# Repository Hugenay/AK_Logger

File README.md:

AK_Logger
=========

test

eine weitere Änderung um zu testen was passiert wenn beide ändern

bla

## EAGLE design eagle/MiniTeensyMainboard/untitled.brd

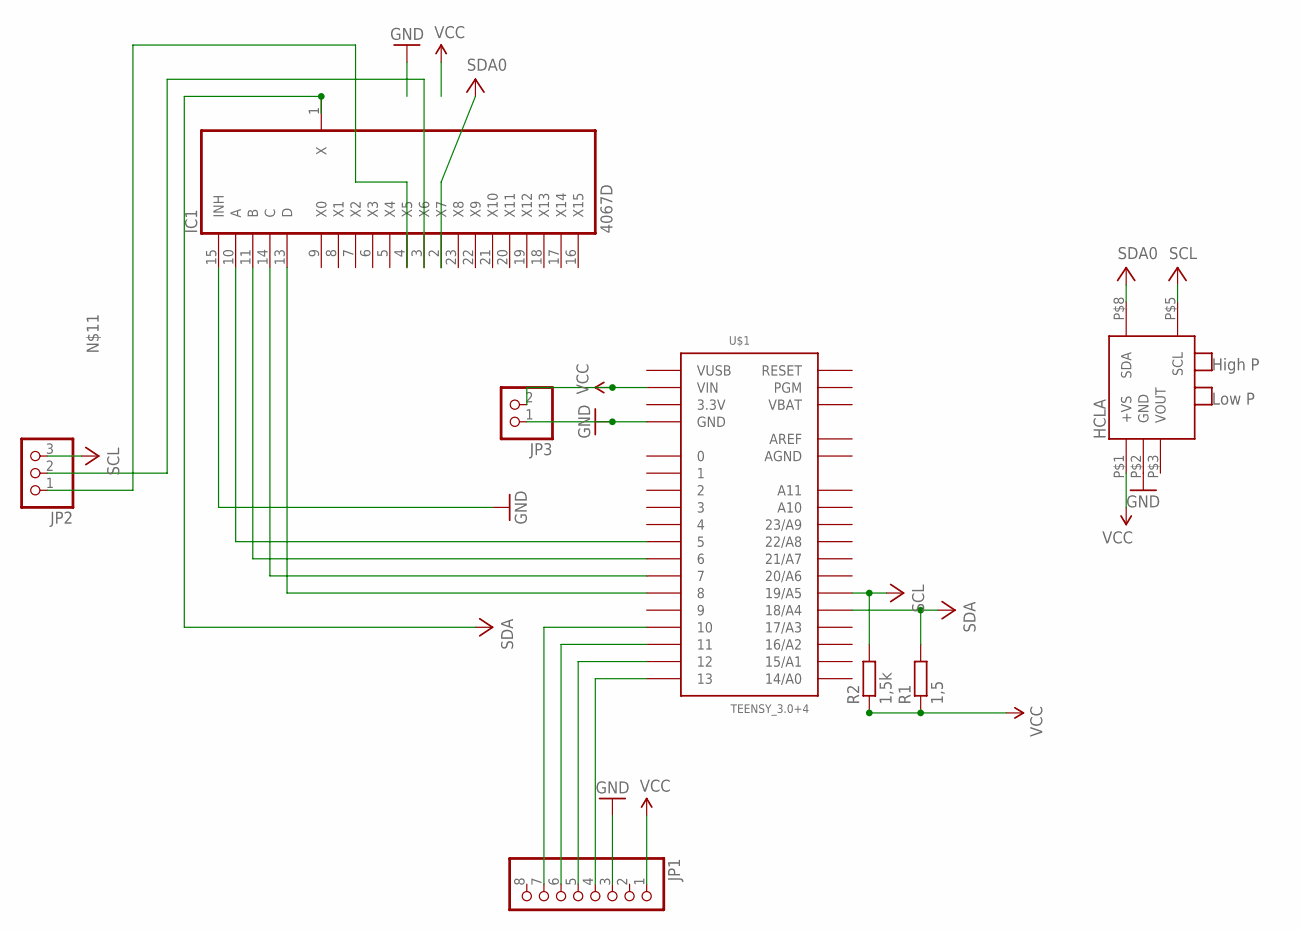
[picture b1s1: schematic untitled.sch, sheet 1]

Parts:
IC1: 4067D; SO24W
JP1: PINHD-1X8; 1X08
JP2: PINHD-1X3; 1X03
JP3: PINHD-1X2; 1X02
R1: 1,5; 0204/5
R2: 1,5k; 0204/5
U$1: TEENSY_3.0+4
U$2: HCLA

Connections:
3.3V: U$1.3.3V, U$1.3.3V1 (3.3V)
AGND: U$1.AGND
AREF: U$1.AREF
GND: IC1.15 (INH), JP1.3, JP3.1, U$1.GND, U$1.GND1 (GND), U$2.P$2 (GND)
unnamed: IC1.10 (A), U$1.5
unnamed: IC1.11 (B), U$1.6
unnamed: IC1.14 (C), U$1.7
unnamed: IC1.13 (D), U$1.8
unnamed: JP1.7, U$1.10
unnamed: JP1.6, U$1.11
unnamed: JP1.5, U$1.12
unnamed: JP1.4, U$1.13
unnamed: IC1.4 (X5), JP2.1
unnamed: IC1.3 (X6), JP2.2
SCL: JP2.3, R2.2, U$1.19/A5, U$2.P$5 (SCL)
SDA: IC1.1 (X), R1.2, U$1.18/A4
SDA0: IC1.2 (X7), U$2.P$8 (SDA)
VBAT: U$1.VBAT
VDD: IC1.24 (VDD), JP1.1, JP3.2, R1.1, R2.1, U$1.VIN, U$2.P$1 (+VS)
VSS: IC1.12 (VSS)
VUSB: U$1.VUSB

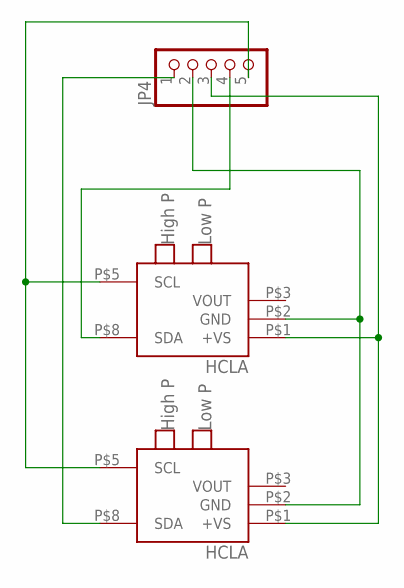
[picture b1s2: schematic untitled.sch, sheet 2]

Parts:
JP4: PINHD-1X5; 1X05
U$3, U$4: HCLA

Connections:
unnamed: JP4.5, U$3.P$5 (SCL), U$4.P$5 (SCL)
unnamed: JP4.3, U$3.P$1 (+VS), U$4.P$1 (+VS)
unnamed: JP4.2, U$3.P$2 (GND), U$4.P$2 (GND)
unnamed: JP4.4, U$3.P$8 (SDA)
unnamed: JP4.1, U$4.P$8 (SDA)

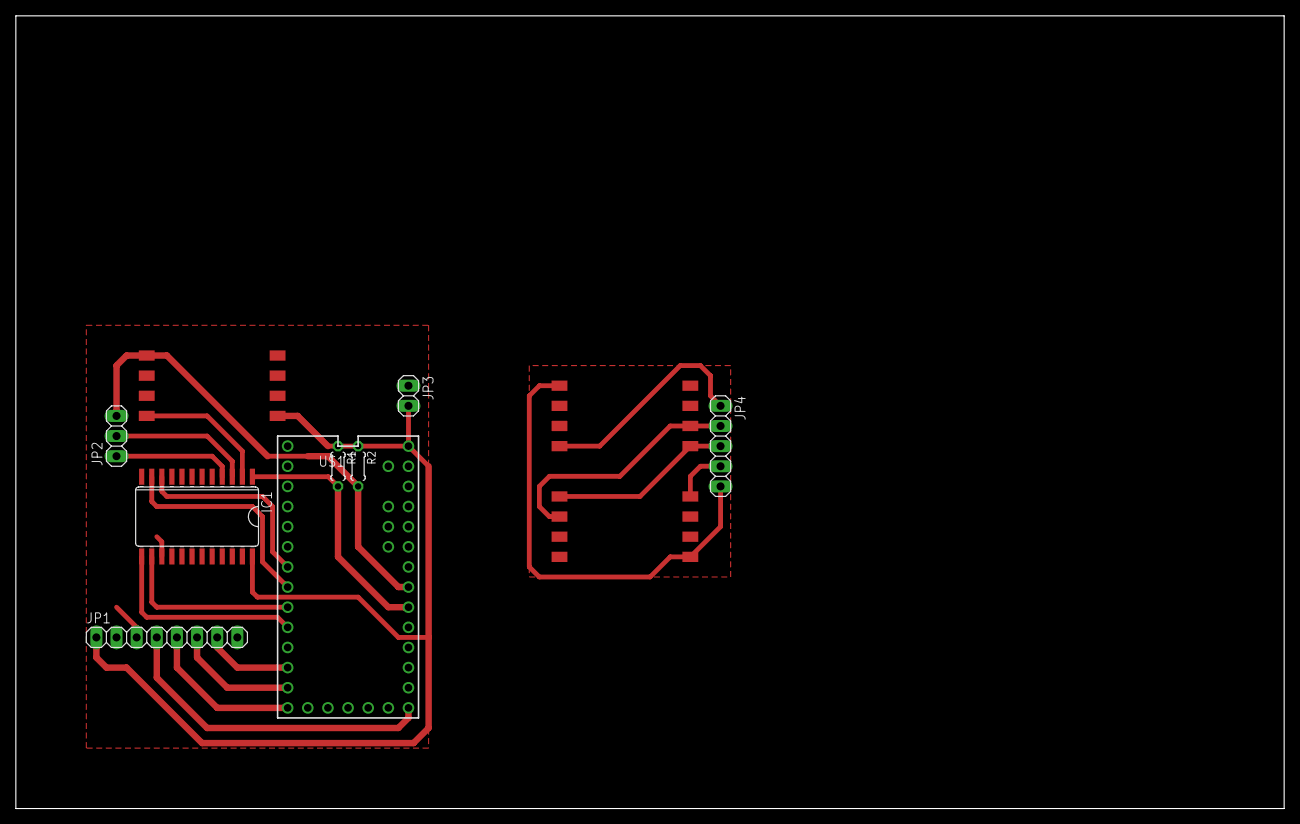
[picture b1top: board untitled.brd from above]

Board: 2 copper layers, 160.0 x 100.0 mm, 11 parts (0 on the bottom side), 21 nets.

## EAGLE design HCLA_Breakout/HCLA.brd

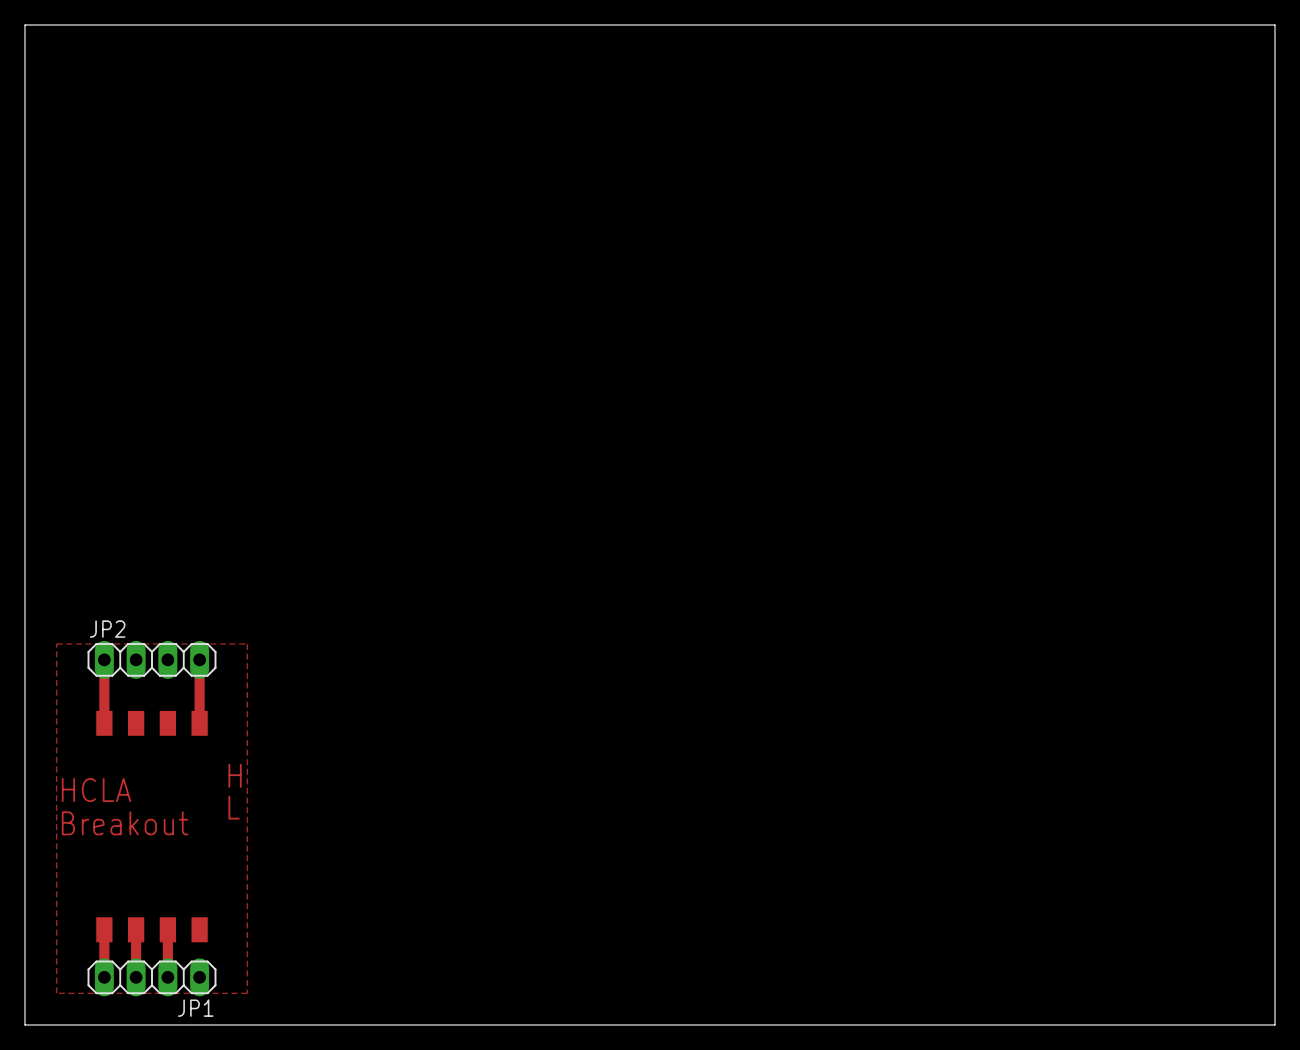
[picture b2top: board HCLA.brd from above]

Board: 2 copper layers, 100.0 x 80.0 mm, 3 parts (0 on the bottom side), 5 nets.

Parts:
JP1, JP2: 1X04
U$1: HCLA

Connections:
+VS: JP1.4, U$1.P$1
GND: JP1.3, U$1.P$2
SCL: JP2.4, U$1.P$5
SDA: JP2.1, U$1.P$8
VOUT: JP1.2, U$1.P$3

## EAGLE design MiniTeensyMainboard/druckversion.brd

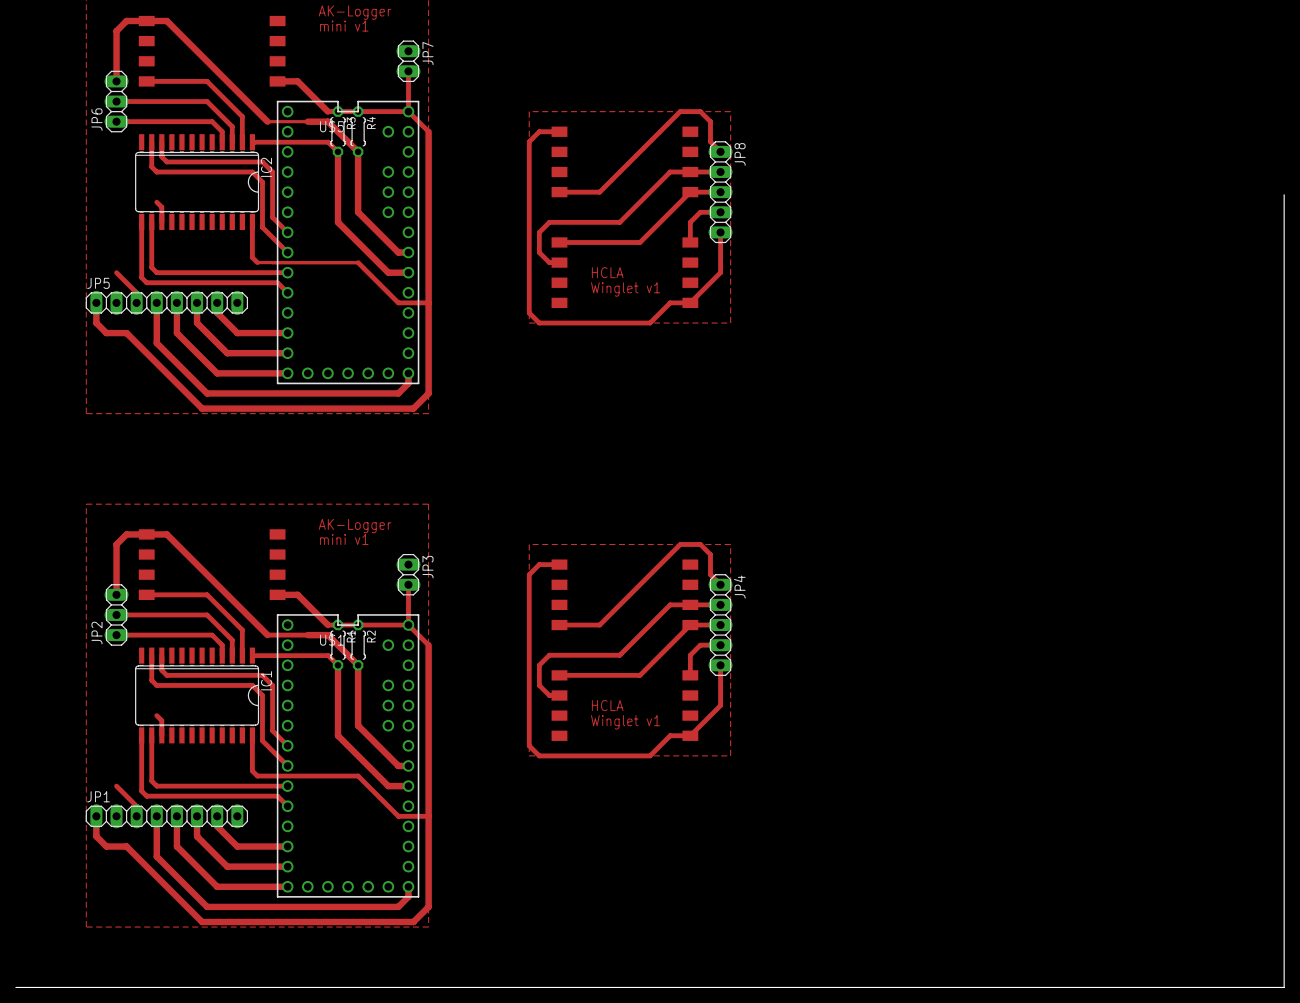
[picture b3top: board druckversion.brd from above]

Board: 2 copper layers, 22 parts (0 on the bottom side), 42 nets.

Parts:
IC1, IC2: 4067D; SO24W
JP1, JP5: 1X08
JP2, JP6: 1X03
JP3, JP7: 1X02
JP4, JP8: 1X05
R1, R3: 1,5; 0204/5
R2, R4: 1,5k; 0204/5
U$1, U$5: TEENSY_3.0+4
U$2, U$3, U$4, U$6, U$7, U$8: HCLA

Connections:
3.3V: U$1.3.3V, U$1.3.3V1
3.3V1: U$5.3.3V, U$5.3.3V1
GND: IC1.15, JP1.3, JP3.1, U$1.GND, U$1.GND1, U$2.P$2
GND1: IC2.15, JP5.3, JP7.1, U$5.GND, U$5.GND1, U$6.P$2
unnamed: IC1.10, U$1.5
unnamed: IC1.11, U$1.6
unnamed: IC1.14, U$1.7
unnamed: IC1.13, U$1.8
unnamed: JP1.7, U$1.10
unnamed: JP1.6, U$1.11
unnamed: JP1.5, U$1.12
unnamed: JP1.4, U$1.13
unnamed: JP4.5, U$3.P$5, U$4.P$5
unnamed: IC1.4, JP2.1
unnamed: IC1.3, JP2.2
unnamed: JP4.3, U$3.P$1, U$4.P$1
unnamed: JP4.2, U$3.P$2, U$4.P$2
unnamed: JP4.4, U$3.P$8
unnamed: JP4.1, U$4.P$8
unnamed: IC2.10, U$5.5
unnamed: IC2.11, U$5.6
unnamed: IC2.14, U$5.7
unnamed: IC2.13, U$5.8
unnamed: JP5.7, U$5.10
unnamed: JP5.6, U$5.11
unnamed: JP5.5, U$5.12
unnamed: JP5.4, U$5.13
unnamed: IC2.4, JP6.1
unnamed: IC2.3, JP6.2
unnamed: JP8.5, U$7.P$5, U$8.P$5
unnamed: JP8.3, U$7.P$1, U$8.P$1
unnamed: JP8.2, U$7.P$2, U$8.P$2
unnamed: JP8.4, U$7.P$8
unnamed: JP8.1, U$8.P$8
SCL: JP2.3, R2.2, U$1.19/A5, U$2.P$5
SCL1: JP6.3, R4.2, U$5.19/A5, U$6.P$5
SDA: IC1.1, R1.2, U$1.18/A4
SDA0: IC1.2, U$2.P$8
SDA1: IC2.2, U$6.P$8
SDA2: IC2.1, R3.2, U$5.18/A4
VDD: IC1.24, JP1.1, JP3.2, R1.1, R2.1, U$1.VIN, U$2.P$1
VDD1: IC2.24, JP5.1, JP7.2, R3.1, R4.1, U$5.VIN, U$6.P$1

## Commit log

2014-02-13 bkla
2014-02-13 Test
2014-02-13 1st commit
2014-02-13 test2
2014-02-13 -neu
2014-02-14 datei wurde geändert um zu testen
2014-02-14 -weitere Änderung
2014-02-23 -test
2014-02-23 ---für test
2014-02-23 --- Test
2014-02-23 Teensy zeug
2014-02-23 -- VS Compiler
2014-03-18 git hub first commit
2014-03-26 Funktionierender Drucksensortest aufm Teensy mit i2c_t3 library
2014-03-26 added SDcard first try
2014-04-16 Mux und SD Karten Funktion
2014-04-16 update Mux und SD-Karte
2014-05-13 migrate to Atmel Studio
2014-05-15 new version
2014-05-16 interrupt sollte jetzt funktionieren
2014-05-16 alter master löschen
2014-05-16 cleanup
2014-05-16 in AK_Logger teensy properties zu Define Projekt hinzugefügt
2014-05-16 define Projekt 2
2014-05-24 micros() in Zeile 101
2014-05-24 ignore update
2014-07-13 Eagle Lib Update
2014-07-13 AK-Logger update
    speichern erst bei Stringlänge = 512 byte
    Schnelleres Speichern mit O_WRITE
2014-07-13 clean repository
    * ignore IDE specific files
    * remove binaries
2014-07-13 reorganize repository – move EAGLE files
2014-07-13 remove empty README

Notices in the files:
parts and their libraries:
SparkFun-Aesthetics: Licensing: Creative Commons ShareAlike 4.0 International - https://creativecommons.org/licenses/by-sa/4.0
